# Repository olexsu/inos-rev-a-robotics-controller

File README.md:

# INOS Rev A 

INOS Rev A is a custom robotics controller developed as a dedicated real-time motion-control node for NVIDIA Jetson-based robotic systems.

The platform follows a distributed control architecture where the NVIDIA Jetson performs high-level functions such as computer vision, AI processing, motion planning, and operator interaction, while the INOS controller executes deterministic real-time functions including motion control, homing, safety monitoring, sensor processing, and hardware management.

The first implementation of the INOS platform is a six-axis robotic arm prototype utilizing stepper motors, external motor drivers, and inductive proximity sensors for joint homing and position reference.

---

# Project Overview

INOS is built around a simple principle:

**High-level intelligence belongs on the Jetson.
Real-time control belongs on dedicated embedded hardware.**

This separation allows the robotics platform to maintain deterministic motion control while leveraging the computational capabilities of NVIDIA Jetson hardware for future AI and machine vision applications.

## NVIDIA Jetson Responsibilities

* Computer vision
* AI processing
* Motion planning
* User interface
* Task execution logic

## INOS Controller Responsibilities

* Multi-axis motion control
* Homing routines
* Safety monitoring
* Sensor processing
* CAN communication
* Hardware management

---

# Hardware Features

* Teensy 4.1 real-time controller
* CAN bus communication with NVIDIA Jetson
* 24V industrial power architecture
* Six-axis robotic arm support
* External STEP/DIR motor driver architecture
* Inductive proximity sensor integration
* Joint homing and position reference system
* Custom 4-layer PCB designed in KiCad
* Modular expansion architecture

---

# System Architecture

```text
Controller / Vision System
            │
            ▼
     NVIDIA Jetson
   (High-Level Control)
            │
         CAN Bus
            │
            ▼
        INOS Rev A
 (Real-Time Controller)
            │
        STEP / DIR
            │
            ▼
 External Driver Board
            │
            ▼
     Stepper Motors
            │
            ▼
 Inductive Homing Sensors
```

---

# Homing and Position Reference

One of the core functions of INOS Rev A is establishing known joint positions after power-up.

Because stepper motors do not inherently know their absolute position when the system starts, each robotic axis uses an inductive proximity sensor as a mechanical reference point.

During initialization:

1. The controller moves each joint toward its reference position.
2. The inductive sensor detects the target.
3. The controller records the reference position.
4. The robot establishes a known coordinate system for all subsequent motion.

This homing architecture allows repeatable positioning and forms the foundation for future inverse kinematics, trajectory planning, and autonomous operation.

---

# Custom Controller Hardware

## Partly Assembled Controller Board — Top

Features:

* Custom 4-layer PCB
* Teensy 4.1 controller
* CAN transceiver
* Sensor interfaces
* Motion-control interfaces
* 24V power architecture
* Expansion capability

---

# PCB Design

## 3D Render

Designed using KiCad and manufactured through JLCPCB.

---

# Development and Validation

## Power-On Testing

## CAN Communication Testing

The INOS Rev A platform has successfully demonstrated:

* Controller board bring-up
* CAN communication
* Multi-axis motion control
* Inductive sensor integration
* Joint homing
* Robotic arm operation
* Embedded firmware validation

---

# Current Status

## Completed

* Custom PCB design
* PCB manufacturing and assembly
* Teensy 4.1 integration
* CAN communication testing
* Multi-axis motion control
* Inductive homing implementation
* Robotic arm prototype integration

## In Progress

* Motion-control refinement
* Safety system development
* CAN protocol expansion
* System optimization

## Planned

* NVIDIA Jetson integration
* Computer vision
* Inverse kinematics
* Autonomous operation
* Agricultural robotics applications

---

# Project Goals

The long-term objective of the INOS platform is to create a scalable robotics architecture capable of supporting:

* Robotic manipulators
* Agricultural automation systems
* Machine vision platforms
* Autonomous robotic applications
* Custom embedded robotics solutions

---

# Development Tools

* KiCad
* Teensy 4.1
* C++
* FlexCAN_T4
* NVIDIA Jetson
* Ubuntu Linux
* GitHub
* JLCPCB

---

# Disclaimer

INOS Rev A is an experimental development platform and active engineering project. The hardware and software are continuously evolving as new features, capabilities, and lessons learned are incorporated into future revisions.

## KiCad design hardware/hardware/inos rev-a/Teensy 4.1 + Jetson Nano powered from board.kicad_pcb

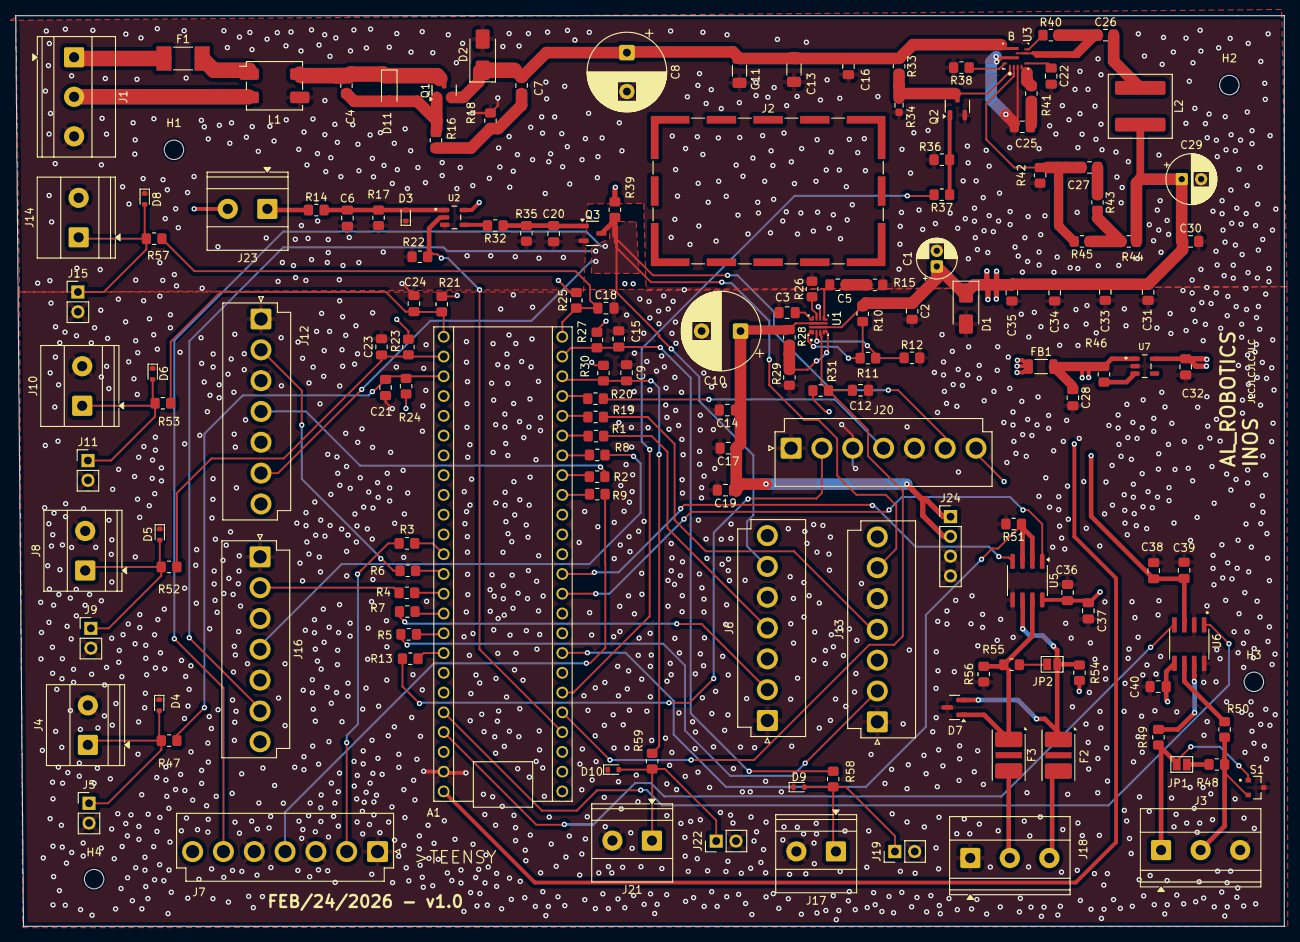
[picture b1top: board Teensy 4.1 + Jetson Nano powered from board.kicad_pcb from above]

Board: 4 copper layers, 163.0 x 117.0 mm, 157 parts (0 on the bottom side), 91 nets.

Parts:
A1: TEENSY_4.1; TEENSY_LONG_EXT
C1: 22uF; CP_Radial_D5.0mm_P2.00mm
C2, C16, C19, C26, C37: 0.1uF; C_0805_2012Metric_Pad1.18x1.45mm_HandSolder
C3: 5.6nF; C_0805_2012Metric_Pad1.18x1.45mm_HandSolder
C4: 10nF; R_0805_2012Metric_Pad1.20x1.40mm_HandSolder
C5, C9, C15, C18, C21, C23, C24: 10nF; C_0805_2012Metric_Pad1.18x1.45mm_HandSolder
C6, C7, C38, C40: 100nF; C_0805_2012Metric_Pad1.18x1.45mm_HandSolder
C8, C10: 470uF; CP_Radial_D10.0mm_P5.00mm
C11, C13: 10uF; C_1206_3216Metric_Pad1.33x1.80mm_HandSolder
C12: 4.7nF; C_0805_2012Metric_Pad1.18x1.45mm_HandSolder
C14, C17, C30, C31, C33, C34, C35: 22uF; C_0805_2012Metric_Pad1.18x1.45mm_HandSolder
C20, C36: 100pF; C_0805_2012Metric_Pad1.18x1.45mm_HandSolder
C22: 47nF; C_0805_2012Metric_Pad1.18x1.45mm_HandSolder
C25: 2.2uF; C_0805_2012Metric_Pad1.18x1.45mm_HandSolder
C27: 150pF; C_0805_2012Metric_Pad1.18x1.45mm_HandSolder
C28, C32: 1 µF; C_0805_2012Metric_Pad1.18x1.45mm_HandSolder
C29: 220uF; CP_Radial_D6.3mm_P2.50mm
C39: 1uF; C_0805_2012Metric_Pad1.18x1.45mm_HandSolder
D1: SMAJ6.0A; D_SMA
D2: SMAJ24A; D_SMA
D3: ESD5Z3V3; D_SOD-523
D4, D5, D6, D8, D9, D10: ESD5Z3.3; D_SOD-523
D7: CDSOT23-SM712; SOT-23
D11: BZT52C15-7-F; D_SOD-123
F1: Fuse; Fuse_Littelfuse-NANO2-451_453
F2, F3: TBU-CA-065-200-WH; Fuse_Bourns_TBU-CA
FB1: BLM31PG121SH1L; L_1206_3216Metric
H1, H2, H3, H4: MountingHole; MountingHole_2.5mm
J1, J3, J18: TB006-508-03BE; TerminalBlock_Phoenix_MKDS-1,5-3-5.08_1x03_P5.08mm_Horizont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
J2: BMI-S-209-F; Laird_Technologies_BMI-S-209-F_29.36x18.50mm
J4, J8, J10, J14, J17, J21, J23: Limit Switch; TerminalBlock_Phoenix_MKDS-1,5-2-5.08_1x02_P5.08mm_Horizont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
J5, J9, J11, J15, J19, J22: Hard limit switch; PinHeader_1x02_P2.54mm_Vertical
J6, J7, J12, J13, J16, J20: Conn_01x07; JST_VH_B7P-VH-B_1x07_P3.96mm_Vertical
J24: Conn_01x04; PinHeader_1x04_P2.54mm_Vertical
JP1, JP2: Jumper_2_Open; SolderJumper-2_P1.3mm_Open_Pad1.0x1.5mm
L1: ACM7060-701-2PL-TL01; L_CommonModeChoke_TDK_ACM7060
L2: XAL7030-332MEC; L_Coilcraft_XAL7030-332
Q1: DMP4065S-7; SOT-23
Q2, Q3: 2N7002; SOT-23-3
R1, R2, R3, R4, R5, R6, R7, R8, R9, R13, R15, R16, R19, R20, R37: 100; R_0805_2012Metric_Pad1.20x1.40mm_HandSolder
R10: 470K; R_0805_2012Metric_Pad1.20x1.40mm_HandSolder
R11: 33.2K; R_0805_2012Metric_Pad1.20x1.40mm_HandSolder
R12: 137K; R_0805_2012Metric_Pad1.20x1.40mm_HandSolder
R14, R47, R52, R53, R57, R58, R59: 1K; R_0805_2012Metric_Pad1.20x1.40mm_HandSolder
R17, R35, R46, R51: 100K; R_0805_2012Metric_Pad1.20x1.40mm_HandSolder
R18, R36, R41: 100k; R_0805_2012Metric_Pad1.20x1.40mm_HandSolder
R21, R23, R24, R25, R27, R30, R31: 10K; R_0805_2012Metric_Pad1.20x1.40mm_HandSolder
R22, R28: 47K; R_0805_2012Metric_Pad1.20x1.40mm_HandSolder
R26: 549; R_0805_2012Metric_Pad1.20x1.40mm_HandSolder
R29: 15.8K; R_0805_2012Metric_Pad1.20x1.40mm_HandSolder
R32: 330; R_0805_2012Metric_Pad1.20x1.40mm_HandSolder
R33: 169k; R_0805_2012Metric_Pad1.20x1.40mm_HandSolder
R34: 36.1k; R_0603_1608Metric_Pad0.98x0.95mm_HandSolder
R38: 52.3k; R_0805_2012Metric_Pad1.20x1.40mm_HandSolder
R39: 4.7K; R_0805_2012Metric_Pad1.20x1.40mm_HandSolder
R40, R43, R49, R50: 0; R_0805_2012Metric_Pad1.20x1.40mm_HandSolder
R42: 10k; R_0805_2012Metric_Pad1.20x1.40mm_HandSolder
R44: 49.9; R_0805_2012Metric_Pad1.20x1.40mm_HandSolder
R45: 73.2k; R_0805_2012Metric_Pad1.20x1.40mm_HandSolder
R48, R55: 120; R_0805_2012Metric_Pad1.20x1.40mm_HandSolder
R54, R56: 680; R_0805_2012Metric_Pad1.20x1.40mm_HandSolder
S1: PESD2CANFD36UU-Q; DIO_PESD2CAN_215
U1: TPS259474LRPWR; IC_TPS25974ARPWR
U2: SN74LVC1G08DBVRE4; SOT95P280X145-5N
U3: TPS56A37RPAR; RPA0010A-MFG
U5: MAX3485ESA+T; SOIC-8_3.9x4.9mm_P1.27mm
U6: TCAN1042HGVDRQ1
U7: TLV75533PDBV

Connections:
3.3VDC out: C32.1, C36.2, C37.1, C40.1, J6.7, J7.7, J12.7, J13.7, J16.7, J20.7, J23.2, R21.1, R23.1, R24.1, R25.1, R27.1, R30.1, R31.2, R39.1, R54.1, U2.5 (VCC), U5.8 (VCC), U6.5 (VIO), U7.5 (OUT)
40-pin header J4 on Jetson: C10.1, C14.1, C17.1, C19.1, J24.1, J24.2, R28.2, U1.6 (OUT)
+5VOUT: C1.1, C2.1, C29.1, C30.1, C31.1, C33.1, C34.1, C35.1, D1.1 (A1), FB1.1, L2.2, R10.1, R44.1, U1.5 (IN)
+5V_LOGIC: A1.VIN, C28.1, C38.1, C39.1, FB1.2, R46.1, U6.3 (VCC), U7.1 (IN)
+24V: F1.1, J1.1
/+24V_RAW: C4.1, D11.1 (K), L1.4, Q1.3 (D)
/EN: Q2.3 (D), R33.2, R34.1, U3.1 (EN)
/EN_GATE: R32.2, U2.4 (Y)
/E_STOP_OK: J23.1, R14.1
/FB: C27.2, R42.1, R45.2, U3.2 (FB)
/Pwr_In: F1.2, L1.1
/SAFETY_OK: C6.1, D3.2 (A), R14.2, R17.1, U2.1 (A)
/SW: C26.1, R40.2, U3.6 (SW)
BUCK_EN Pin #4: A1.D4, R37.2
CAN1 RX D23: A1.D23 (A9), U6.4 (RXD)
CAN1 TX D22: A1.D22 (A8), U6.1 (TXD)
Dir1 D24: J7.4, R9.2
Dir2 D25: J12.4, R2.2
Dir3 D26: J16.4, R8.2
Dir4 D27: J6.4, R1.2
Dir5 D28: J13.4, R19.1
Dir6 D29: J20.4, R20.1
EFUSE_PG PIN # 3: A1.D3, C12.1, R31.1, U1.3 (PG)
GLOBAL_EN_N: J6.6, J7.6, J12.6, J13.6, J16.6, J20.6, Q3.3 (D), R39.2
GND: A1.AGND/GND, C1.2, C2.2, C3.2, C6.2, C8.2, C9.2, C10.2, C11.2, C12.2, C13.2, C14.2, C15.2, C16.2, C17.2, C18.2, C19.2, C20.2, C21.2, C22.2, C23.2, C24.2, C25.2, C28.2, C29.2, C30.2, C31.2, C32.2, C33.2, C34.2, C35.2, C36.1, C37.2, C38.2, C39.2, C40.2, D1.2 (A2), D2.2 (A2), D3.1 (K), D4.1 (K), D5.1 (K), D6.1 (K), D7.3, D8.1 (K), D9.1 (K), D10.1 (K), J1.3, J3.3, J4.2, J5.2, J6.1, J6.3, J6.5, J7.1, J7.3, J7.5, J8.2, J9.2, J10.2, J11.2, J12.1, J12.3, J12.5, J13.1, J13.3, J13.5, J14.2, J15.2, J16.1, J16.3, J16.5, J17.2, J18.1, J19.2, J20.1, J20.3, J20.5, J21.2, J22.2, J24.3, J24.4, L1.3, Q2.2 (S), Q3.2 (S), R12.2, R15.2, R17.2, R18.2, R22.2, R26.2, R29.1, R34.2, R35.2, R36.1, R38.2, R42.2, R51.2, R56.2, S1.3, U1.8 (GND), U2.3 (GND), U3.3 (AGND), U3.9 (PGND), U5.5 (GND), U6.2 (GND), U6.8 (STB), U7.2 (GND)
LIM1 D30: A1.D30, C9.1, R30.2, R59.2
LIM2 D31: A1.D31, C15.1, R27.2, R58.2
LIM3 D32: A1.D32, C18.1, R25.2, R57.2
LIM4 D33: A1.D33, C24.1, R21.2, R53.2
LIM5 D34: A1.D34, C23.1, R23.2, R52.2
LIM6 D35: A1.D35, C21.1, R24.2, R47.2
MOTION_ALLOWED PIN#2: A1.D2, R22.1, U2.2 (B)
unnamed: A1.D14 (A0), R3.1
unnamed: A1.D15 (A1), R6.1
unnamed: A1.D16 (A2), R4.1
unnamed: A1.D17 (A3), R7.1
unnamed: A1.D18 (A4), R5.1
unnamed: A1.D19 (A5), R13.1
unnamed: A1.D24 (A10), R9.1
unnamed: A1.D25 (A11), R2.1
unnamed: A1.D26 (A12), R8.1
unnamed: A1.D27 (A13), R1.1
unnamed: A1.D28, R19.2
unnamed: A1.D29, R20.2
unnamed: C5.1, R15.1
unnamed: C7.2, R16.2, R18.1
unnamed: C25.1, R41.2
unnamed: C26.2, L2.1
unnamed: C27.1, R43.1
unnamed: C7.1, C8.1, C11.1, C13.1, C16.1, D2.1 (A1), Q1.2 (S), R33.1, U3.8 (VIN)
unnamed: D4.2 (A), J4.1, J5.1, R47.1
unnamed: D5.2 (A), J8.1, J9.1, R52.1
unnamed: D6.2 (A), J10.1, J11.1, R53.1
unnamed: D8.2 (A), J14.1, J15.1, R57.1
unnamed: D9.2 (A), J17.1, J19.1, R58.1
unnamed: D10.2 (A), J21.1, J22.1, R59.1
unnamed: C4.2, D11.2 (A), Q1.1 (G), R16.1
unnamed: J1.2, L1.2
unnamed: J3.1, JP1.2 (B), R49.2, S1.1
unnamed: J3.2, R48.1, R50.2, S1.2
unnamed: F3.3, J18.2
unnamed: F2.3, J18.3
unnamed: JP1.1 (A), R48.2
unnamed: JP2.1 (A), R55.1
unnamed: D7.2, F2.1, JP2.2 (B), R54.2, U5.6 (A)
unnamed: Q2.1 (G), R36.2, R37.1
unnamed: C20.1, Q3.1 (G), R32.1, R35.1
unnamed: R43.2, R44.2, R45.1
unnamed: R10.2, R11.1, U1.1 (EN_UVLO)
unnamed: R26.1, U1.9 (ILM)
unnamed: C3.1, U1.10 (ITIMER)
unnamed: R11.2, R12.1, U1.2 (OVLO)
unnamed: R28.1, R29.2, U1.4 (PGTH)
unnamed: C5.2, U1.7 (dVdt)
unnamed: R40.1, U3.7 (BOOT)
unnamed: R38.1, U3.10 (MODE)
unnamed: R41.1, U3.4 (PG)
unnamed: C22.1, U3.5 (SS)
unnamed: D7.1, F3.1, R55.2, R56.1, U5.7 (B)
unnamed: R49.1, U6.7 (CANH)
unnamed: R50.1, U6.6 (CANL)
unnamed: R46.2, U7.3 (EN)
RS485_DE D6: A1.D6, R51.1, U5.2 (~RE), U5.3 (DE)
RS485_RX D9: A1.D9, U5.1 (RO)
RS485_TX D10: A1.D10 ((CS)D10), U5.4 (DI)
Step1 D14: J7.2, R3.2
Step2 D15: J12.2, R6.2
Step3 D16: J16.2, R4.2
Step4 D17: J6.2, R7.2
Step5 D18: J13.2, R5.2
Step6 D19: J20.2, R13.2

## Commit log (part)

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2026-06-06 Enhance README with project details and features
    Expanded the README to include detailed project description, key features, system architecture, design philosophy, current status, and project goals.
2026-06-06 Revise README for clarity and detail enhancement
    Expanded project overview and clarified responsibilities of NVIDIA Jetson and INOS controller. Updated hardware features and current status sections for better clarity.
2026-06-06 Add images to photos README
    Added multiple images to README for project documentation.
2026-06-06 Revise README for clarity and image updates
    Updated the README.md to enhance clarity and fix image references.
2026-06-06 Create photos
2026-06-06 Add test.txt with initial content
2026-06-06 Update image references in README.md
    Updated image references in README to reflect new filenames and versions.
2026-06-06 Create hardware
2026-06-06 Update section title for controller board
2026-06-08 Update image for INOS Rev A Board Bottom
2026-06-11 Add files via upload
    Added INOS Rev B schematic PDF.
    Rev B documents the updated robotic arm controller design, including:
    - 24V protected system input
    - 19V Jetson Orin Nano Developer Kit power output
    - 24V to 5V logic buck section
    - 5V / 3.3V logic rails
2026-06-28 Update 3D render image in README
2026-06-28 Rename inos_rev_b_pcb_layout.png to inos_rev_a_pcb_layout.png
2026-06-28 Remove PCB Layout section from README
    Removed PCB Layout section and its image from README.
